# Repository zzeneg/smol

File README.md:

# Smol

Small and cheap low profile split keyboard with 36 keys using RP2040 Zero microcontrollers.

## Features

- 36 keys
- low profile choc switches with hotswap and choc spacing
- per-key RGB matrix
- Waveshare RP2040 Zero controller
- QMK firmware
- TRRS connection between splits (can use USB-C instead but not recommended, too low for many cables)
- Panasonic EVQWGD001 roller encoder (left side only) or EC11 rotary encoder (both sides)

## Photos

## Gerber files

- [PCB](gerbers/pcb.zip)

## Case files

In [STL folder](./stl/) - files for left/right parts. Left also has a version for roller encoder (make sure to order both top and bottom with roller).

## Bill of materials

_Prices for EU with taxes and shipping_

Total cost with required parts: **$42**

- PCBs - $6 (JLCPCB)
- Case (4 parts) - $13 (JLCPCB, white resin)
- 2 Waveshare [RP2040 Zero](https://www.aliexpress.com/item/3256804090654134.html) MCUs - $8.5
- 36 [SMD SOD-123 1N4148](https://www.aliexpress.com/item/1005002882901030.html) diodes - $2
- 1 or 2 [EC11/12 rotary encoder](https://www.aliexpress.com/item/33006686909.html) with [knob](https://www.aliexpress.com/item/1005003425428192.html) - $5
- [Panasonic EVQWGD001 roller encoder](https://www.aliexpress.com/item/32990950196.html) - $9, optional
- 6mm M2 [screws with flat head](https://www.aliexpress.com/item/4001248931159.html) and [nuts](https://www.aliexpress.com/item/1005001412230125.html) - $4
- [TRRS PJ-320A](https://www.aliexpress.com/item/4000661212458.html) connectors - $1.5
- [TRRS cable](https://www.aliexpress.com/item/1005003676559658.html) - $2
- [RGB LEDs](https://www.aliexpress.com/item/1005003636607308.html) - $8.5, optional

## Firmware

QMK:

- [source code](https://github.com/zzeneg/qmk_firmware/tree/feature/smol/keyboards/smol)
- [pre-compiled file](./firmware/qmk/smol_zzeneg.uf2)

Vial:

- [source code](https://github.com/zzeneg/vial-qmk/tree/feature/smol/keyboards/smol)
- [pre-compiled file](./firmware/vial/smol_vial.uf2)

## Changelog

- 2023-06-25 - new case with magnet and feet holes, new Fusion 360 project with design history

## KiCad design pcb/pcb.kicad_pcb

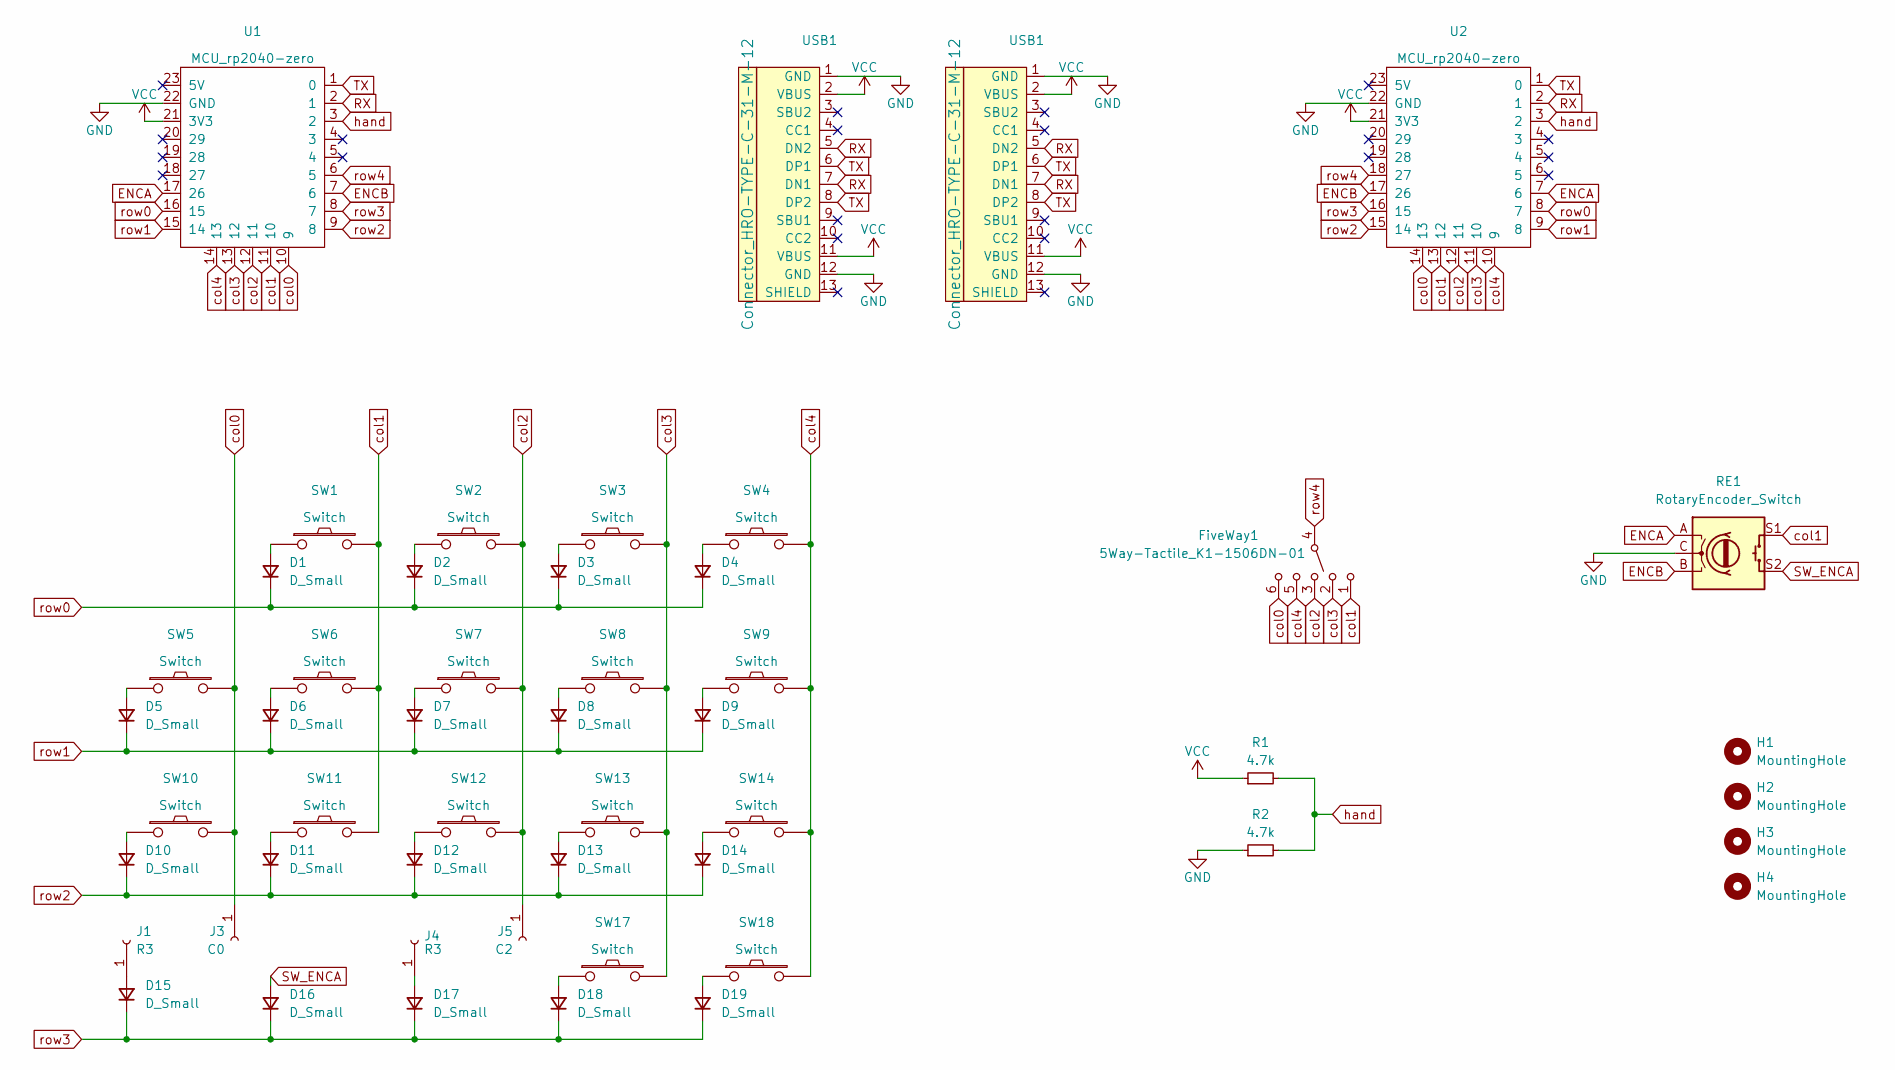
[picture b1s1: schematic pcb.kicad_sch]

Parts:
D1, D2, D3, D4, D5, D6, D7, D8, D9, D10, D11, D12, D13, D14, D15, D16, D17, D18, D19: D_Small; Diode_1N4148-SOD123-no-label-reversible-flip3d
FiveWay1: 5Way-Tactile_K1-1506DN-01; Button_5way
H1, H2, H3, H4: MountingHole; Hole_M2-spacer
J1, J4: R3; PinHeader_1x01_P2.54mm_Vertical
J3: C0; PinHeader_1x01_P2.54mm_Vertical
J5: C2; PinHeader_1x01_P2.54mm_Vertical
R1, R2: 4.7k; R_1206_3216Metric_Pad1.30x1.75mm_HandSolder
RE1: RotaryEncoder_Switch; RotaryEncoder_EC11-reversible
SW1, SW2, SW3, SW4, SW5, SW6, SW7, SW8, SW9, SW10, SW11, SW12, SW13, SW14: Switch; Switch_MX-hotswap-miny-reversible
SW17, SW18: Switch; Switch_KS-miny-reversible-hotswap-south
U1, U2: MCU_rp2040-zero; MCU_rp2040-zero-smd
USB1: Connector_HRO-TYPE-C-31-M-12; Connector_HRO-TYPE-C-31-M-12-data

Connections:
ENCA: RE1.A, U1.17 (26), U2.7 (6)
ENCB: RE1.B, U1.7 (6), U2.17 (26)
GND: R2.1, RE1.C, U1.22 (GND), U2.22 (GND), USB1.1 (GND), USB1.12 (GND); also elsewhere on the board
unnamed: D1.2 (A), SW1.1
unnamed: D2.2 (A), SW2.1
unnamed: D3.2 (A), SW3.1
unnamed: D4.2 (A), SW4.1
unnamed: D5.2 (A), SW5.1
unnamed: D6.2 (A), SW6.1
unnamed: D7.2 (A), SW7.1
unnamed: D8.2 (A), SW8.1
unnamed: D9.2 (A), SW9.1
unnamed: D10.2 (A), SW10.1
unnamed: D11.2 (A), SW11.1
unnamed: D12.2 (A), SW12.1
unnamed: D13.2 (A), SW13.1
unnamed: D14.2 (A), SW14.1
unnamed: D15.2 (A), J1.1
unnamed: D17.2 (A), J4.1
unnamed: D18.2 (A), SW17.1
unnamed: D19.2 (A), SW18.1
RX: U1.2 (1), U2.2 (1), USB1.5 (DN2), USB1.7 (DN1); also elsewhere on the board
SW_ENCA: D16.2 (A), RE1.S2
TX: U1.1 (0), U2.1 (0), USB1.6 (DP1), USB1.8 (DP2); also elsewhere on the board
VCC: R1.1, U1.21 (3V3), U2.21 (3V3), USB1.2 (VBUS), USB1.11 (VBUS); also elsewhere on the board
col0: FiveWay1.6, J3.1, SW5.2, SW10.2, U1.10 (9), U2.14 (13)
col1: FiveWay1.1, RE1.S1, SW1.2, SW6.2, SW11.2, U1.11 (10), U2.13 (12)
col2: FiveWay1.3, J5.1, SW2.2, SW7.2, SW12.2, U1.12 (11), U2.12 (11)
col3: FiveWay1.2, SW3.2, SW8.2, SW13.2, SW17.2, U1.13 (12), U2.11 (10)
col4: FiveWay1.5, SW4.2, SW9.2, SW14.2, SW18.2, U1.14 (13), U2.10 (9)
hand: R1.2, R2.2, U1.3 (2), U2.3 (2)
row0: D1.1 (K), D2.1 (K), D3.1 (K), D4.1 (K), U1.16 (15), U2.8 (7)
row1: D5.1 (K), D6.1 (K), D7.1 (K), D8.1 (K), D9.1 (K), U1.15 (14), U2.9 (8)
row2: D10.1 (K), D11.1 (K), D12.1 (K), D13.1 (K), D14.1 (K), U1.9 (8), U2.15 (14)
row3: D15.1 (K), D16.1 (K), D17.1 (K), D18.1 (K), D19.1 (K), U1.8 (7), U2.16 (15)
row4: FiveWay1.4, U1.6 (5), U2.18 (27)

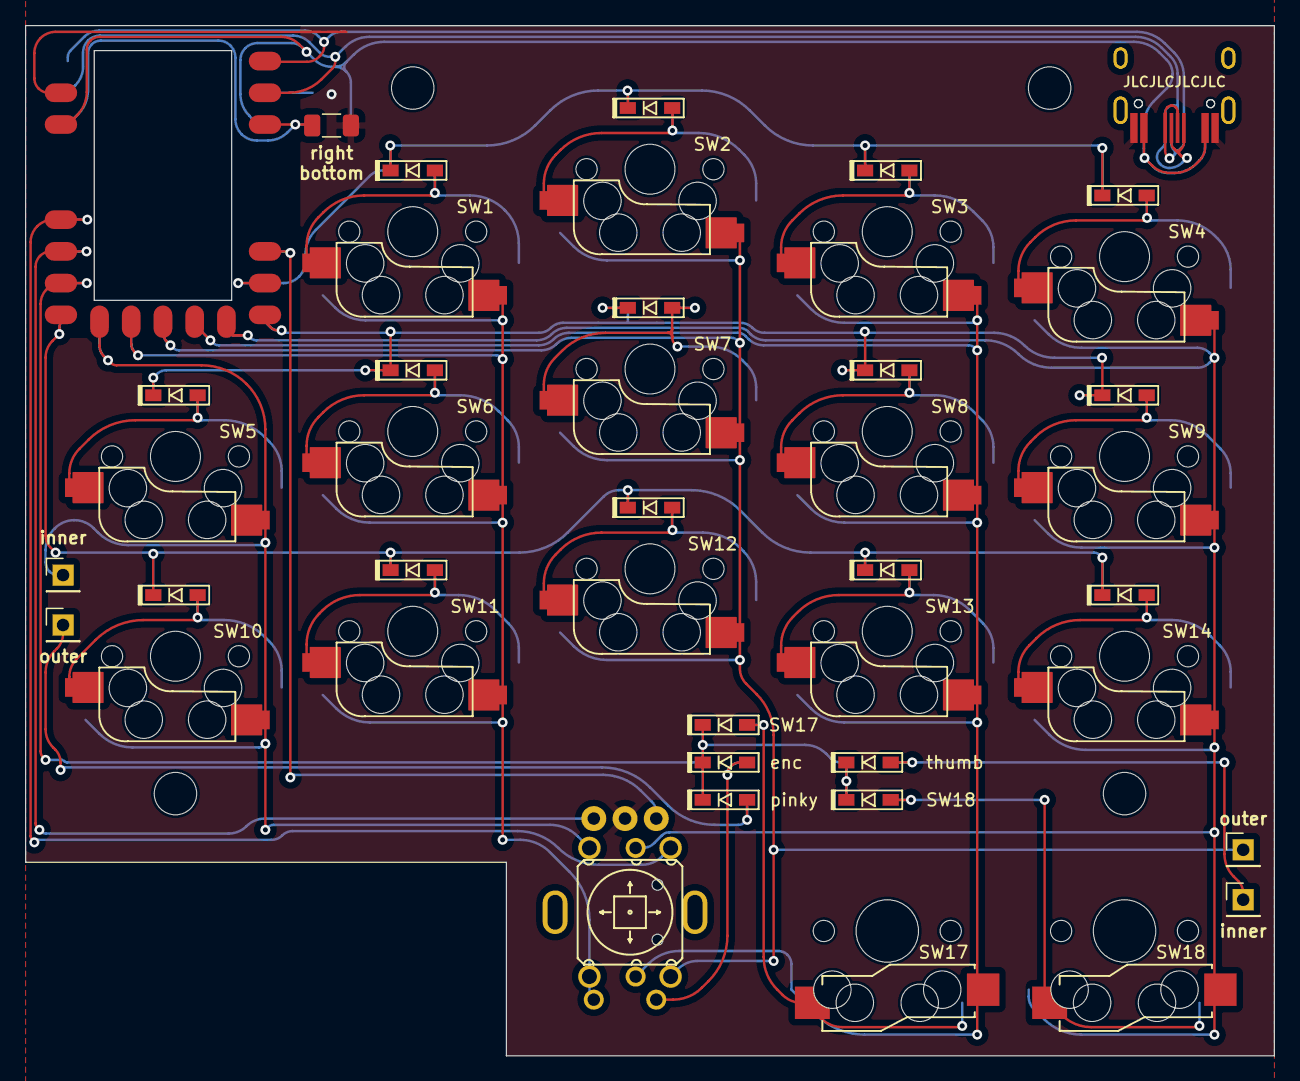
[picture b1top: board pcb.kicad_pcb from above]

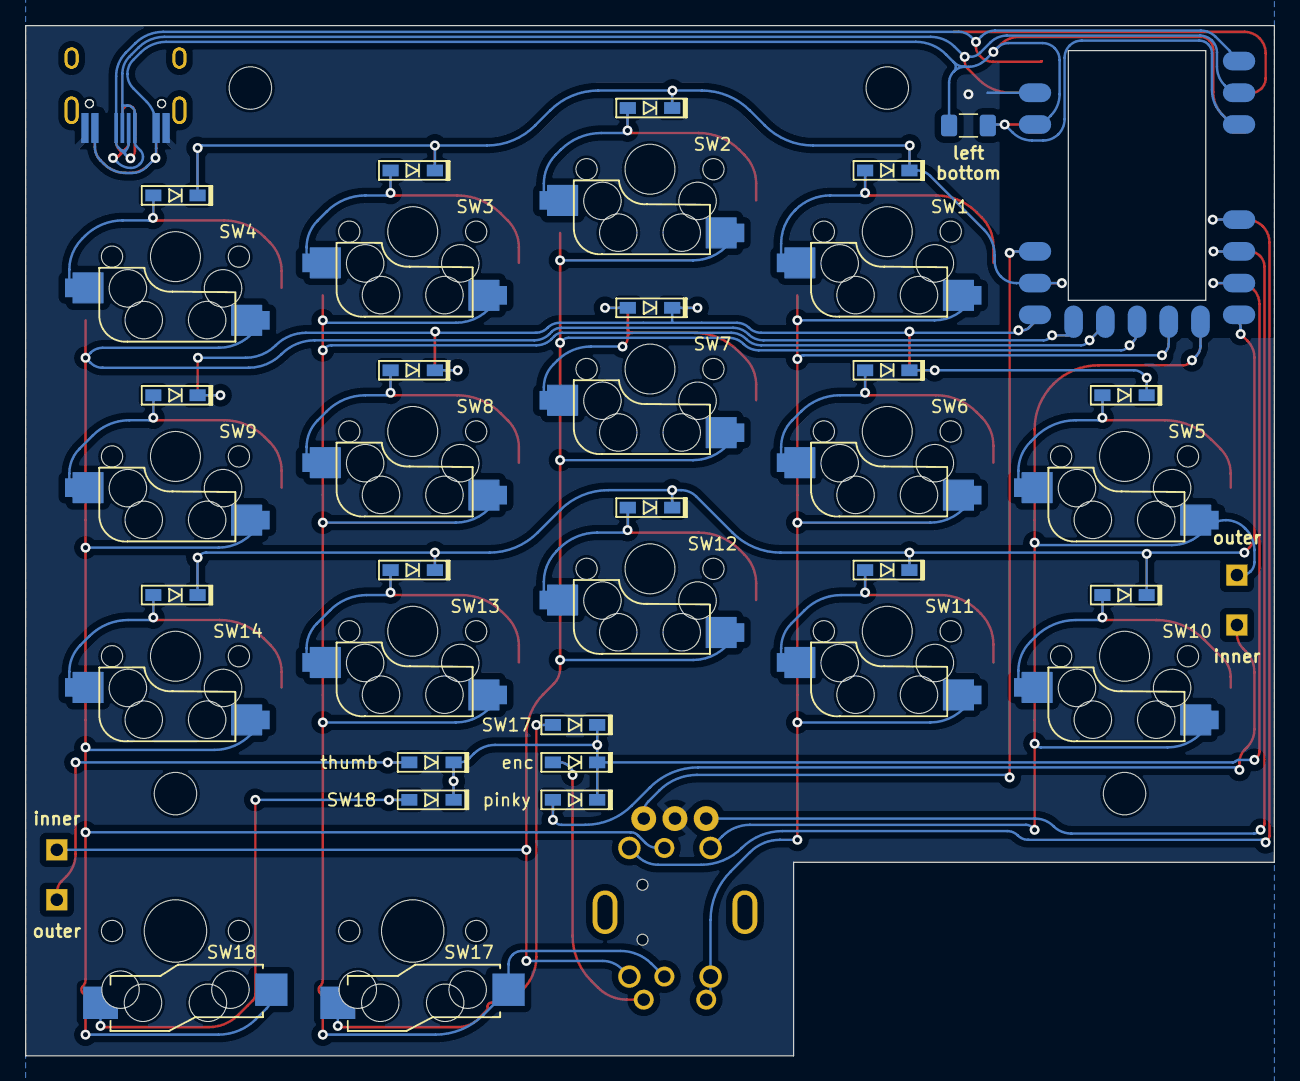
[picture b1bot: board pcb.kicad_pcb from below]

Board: 2 copper layers, 100.0 x 82.5 mm, 51 parts (22 on the bottom side), 36 nets.

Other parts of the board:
USB2: Connector_HRO-TYPE-C-31-M-12; Connector_HRO-TYPE-C-31-M-12-data

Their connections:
GND: USB2.1 (GND), USB2.12 (GND); also elsewhere on the board
RX: USB2.5 (DN2), USB2.7 (DN1); also elsewhere on the board
TX: USB2.6 (DP1), USB2.8 (DP2); also elsewhere on the board
VCC: USB2.2 (VBUS), USB2.11 (VBUS); also elsewhere on the board

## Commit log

2023-03-12 add pcb
2023-03-13 add case
2023-03-13 readme
2023-03-15 add QMK firmware
2023-05-15 add vial firmware
2023-06-25 new case
2023-07-03 fix new case
2023-07-03 small PCB updates
2023-07-13 small case updates
2023-11-07 use alps smd 5way
2024-02-15 new pcb
2024-02-15 improve labels
2024-02-16 rounded tracks
2024-02-16 add DES keycaps
2024-02-19 fix keycaps
